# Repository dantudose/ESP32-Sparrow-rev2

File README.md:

# ESP32-Sparrow-rev2

The ESP32 Sparrow is a development board supporting the ESP32-WROVER module. It is fully Arduino-compatible and it comes with the following features:
* BME680 temperature, humidity, pressure and air quality sensor
* LTR308 ambient light sensor/luxmeter
* 128x32 SSD1306 OLED
* RGB LED
* I2S Microphone
* Micro-SD Card Holder
* 18650 LiPo battery holder with charging circuit
* Expansion headers
* USB charging/programming and data interface

<div id="cover">

</div>

Repository Contents
-------------------

* **/Hardware** - Eagle design files (.brd, .sch)
* **/Images** - Pinout and board images

Documentation
--------------
* **[Hookup Guide](https://ocw.cs.pub.ro/courses/iothings/laboratoare/2022/lab1)** - Basic hookup tutorial for ESP32 Sparrow

License Information
-------------------

This product is _**open source**_! 

Please review the LICENSE file for license information. 

Distributed as-is; no warranty is given.

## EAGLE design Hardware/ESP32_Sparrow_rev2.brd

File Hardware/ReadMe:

ESP32 Sparrow rev2 Eagle CAD files

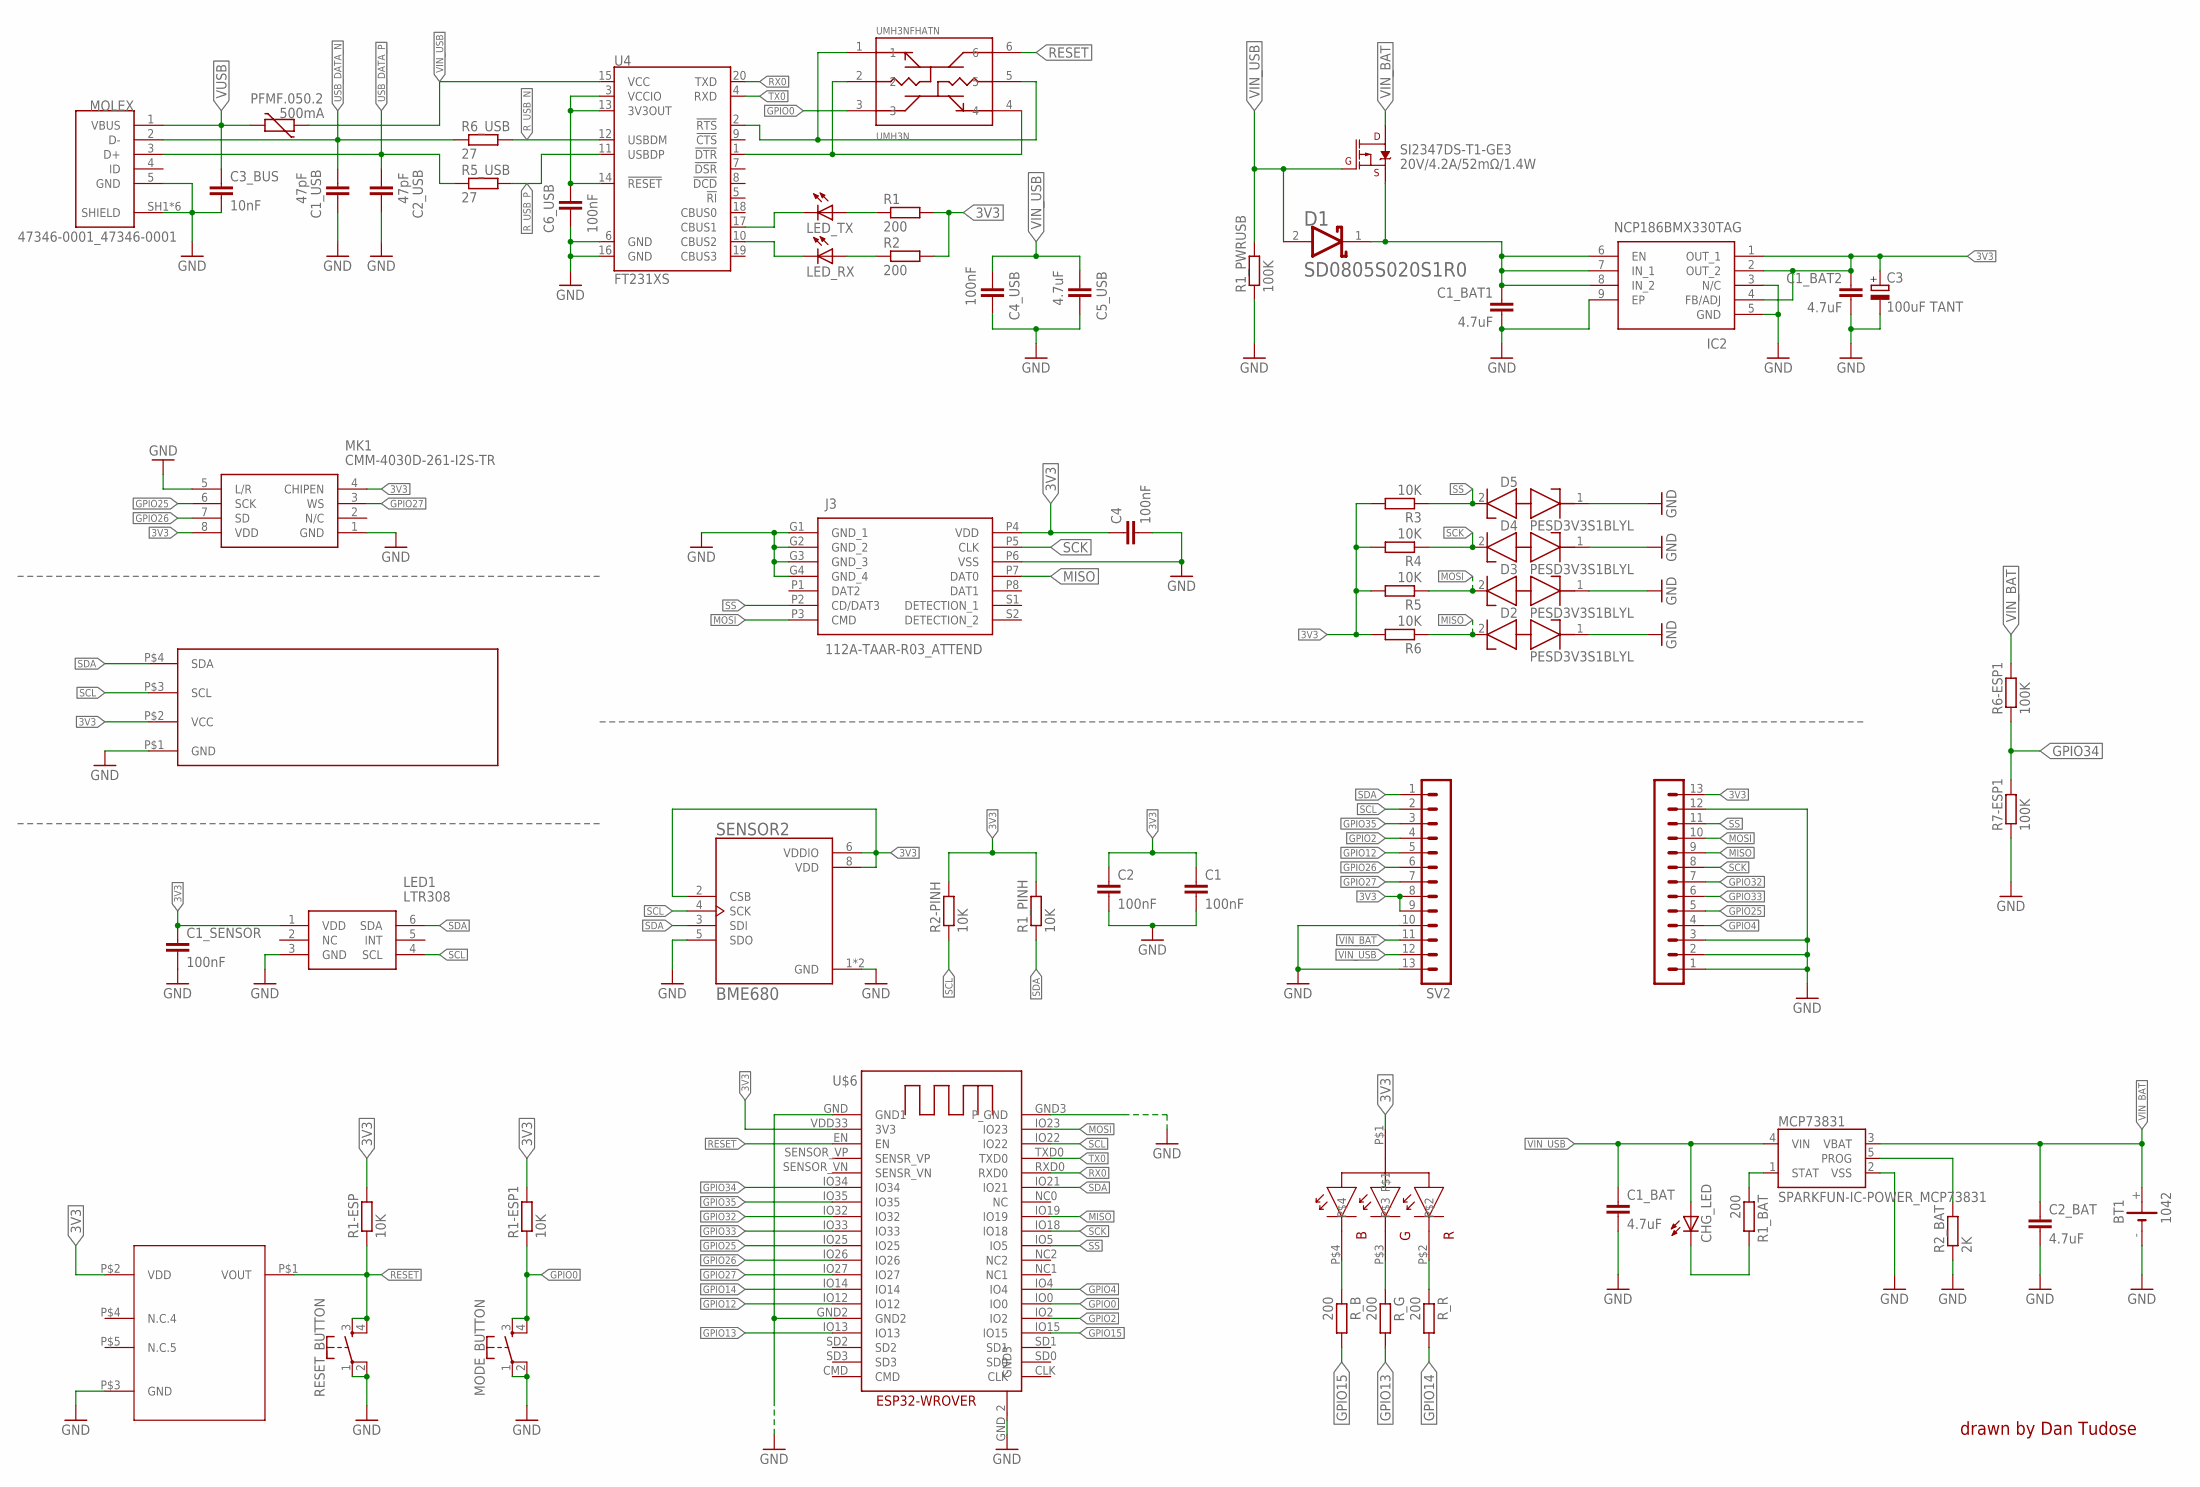
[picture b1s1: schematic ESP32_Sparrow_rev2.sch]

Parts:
BD48E27G-TR: BD48E27G-TR_BD48E27G-TR; BD48E27G-TR_SSOP5
BT1: 1042; BAT_1042
C1, C2, C4: 100nF; EAGLE-LTSPICE_C0402
C1_BAT, C1_BAT1, C1_BAT2, C2_BAT, C5_USB: 4.7uF; RCL_C0603
C1_SENSOR, C4_USB, C6_USB: 100nF; RCL_C0603
C1_USB, C2_USB: 47pF; RCL_C0603
C3: 100uF TANT; CT3528
C3_BUS: 10nF; RCL_C0603
CHG_LED: ADAFRUIT_LEDCHIP-LED0603; ADAFRUIT_CHIP-LED0603
D1: AVX---SD0805S020S1R0_AVX_SD0805S020S1R0AVX_SD0805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; AVX---SD0805S020S1R0_AVX_SD0805S020S1R0_0
D2, D3, D4, D5: PESD3V3S1BLYL; PESD5V0S1BL315
IC2: NCP186BMX330TAG; NCP186AMX330TAG
J3: 112A-TAAR-R03_ATTEND; 112ATAARR03ATTEND
LED1: LTR308; SAMACSYS_PARTS_LTR303ALS01
LED_RX: ADAFRUIT_LEDCHIP-LED0603; ADAFRUIT_CHIP-LED0603
LED_TX: ADAFRUIT_LEDCHIP-LED0603; ADAFRUIT_CHIP-LED0603
MCP73831: SPARKFUN-IC-POWER_MCP73831; SPARKFUN-IC-POWER_SOT23-5
MK1: CMM-4030D-261-I2S-TR; CMM4030D261I2STR
MODE_BUTTON: SPARKFUN-SWITCHES_MOMENTARY-SWITCH-SPST-2-SMD-4.6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; SPARKFUN-SWITCHES_TACTILE_SWITCH_SMD_4.6X2.8MM
MOLEX: 47346-0001_47346-0001; 47346-0001_MOLEX_47346-0001
PFMF.050.2: 500mA; VARISTOR_CT/CN1812
R1, R1_BAT, R2: 200; EAGLE-LTSPICE_R0402
R1-ESP, R1-ESP1, R1_PINH, R2-PINH, R3, R4, R5, R6: 10K; EAGLE-LTSPICE_R0402
R1_PWRUSB, R6-ESP1, R7-ESP1: 100K; EAGLE-LTSPICE_R0402
R2_BAT: 2K; EAGLE-LTSPICE_R0402
R5_USB, R6_USB: 27; EAGLE-LTSPICE_R0402
RESET_BUTTON: SPARKFUN-SWITCHES_MOMENTARY-SWITCH-SPST-2-SMD-4.6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; SPARKFUN-SWITCHES_TACTILE_SWITCH_SMD_4.6X2.8MM
R_B: 200; EAGLE-LTSPICE_R0402
R_G: 200; EAGLE-LTSPICE_R0402
R_R: 200; EAGLE-LTSPICE_R0402
SENSOR2: BME680; BME680_PSON80P300X300X100-8N
SI2347DS-T1-GE3: 20V/4.2A/52mΩ/1.4W; SPARKFUN-DISCRETESEMI_SOT23-3
SV1, SV2: MA13-1
U4: FT231XS; SPARKFUN-IC-COMMS_SSOP20_L
U$1: OLED; SIP
U$2: 150202M153130_150202M153130-RGB; 150202M153130_150202M153130
U$6: ESP32-WROVER_ESP32-WROVER
UMH3NFHATN: UMH3N; UMH3N_SOP65P210X100-6N

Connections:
3V3: BD48E27G-TR.P$2 (VDD), C1.1, C1_BAT2.1, C1_SENSOR.1, C2.1, C3.+, C4.1, IC2.1 (OUT_1), IC2.2 (OUT_2), IC2.4 (FB/ADJ), J3.P4 (VDD), LED1.1 (VDD), MK1.4 (CHIPEN), MK1.8 (VDD), R1.2, R1-ESP.2, R1-ESP1.2, R1_PINH.2, R2.2, R2-PINH.2, R3.2, R4.2, R5.2, R6.2, SENSOR2.2 (CSB), SENSOR2.6 (VDDIO), SENSOR2.8 (VDD), SV1.13, SV2.8, SV2.9, U$1.P$2 (VCC), U$2.P$1, U$6.VDD33 (3V3)
GND: BD48E27G-TR.P$3 (GND), BT1.-, C1.2, C1_BAT.2, C1_BAT1.2, C1_BAT2.2, C1_SENSOR.2, C1_USB.2, C2.2, C2_BAT.2, C2_USB.2, C3.-, C3_BUS.2, C4.2, C4_USB.2, C5_USB.2, C6_USB.2, D2.1 (K1), D3.1 (K1), D4.1 (K1), D5.1 (K1), IC2.3 (N/C), IC2.5 (GND), IC2.9 (EP), J3.G1 (GND_1), J3.G2 (GND_2), J3.G3 (GND_3), J3.G4 (GND_4), J3.P6 (VSS), LED1.3 (GND), MCP73831.2 (VSS), MK1.1 (GND), MK1.5 (L/R), MODE_BUTTON.1, MODE_BUTTON.2, MOLEX.5 (GND), MOLEX.SH1 (SHIELD), MOLEX.SH2 (SHIELD), MOLEX.SH3 (SHIELD), MOLEX.SH4 (SHIELD), MOLEX.SH5 (SHIELD), MOLEX.SH6 (SHIELD), R1_PWRUSB.1, R2_BAT.1, R7-ESP1.1, RESET_BUTTON.1, RESET_BUTTON.2, SENSOR2.1 (GND), SENSOR2.5 (SDO), SENSOR2.7 (GND), SV1.1, SV1.2, SV1.3, SV1.12, SV2.10, SV2.13, U4.6 (GND), U4.16 (GND), U$1.P$1 (GND), U$6.GND (GND1), U$6.GND2, U$6.GND3 (P_GND), U$6.GND_2 (GND3)
GPIO0: MODE_BUTTON.3, MODE_BUTTON.4, R1-ESP1.1, U$6.IO0, UMH3NFHATN.3
GPIO2: SV2.4, U$6.IO2
GPIO4: SV1.4, U$6.IO4
GPIO12: SV2.5, U$6.IO12
GPIO13: R_G.2, U$6.IO13
GPIO14: R_R.2, U$6.IO14
GPIO15: R_B.2, U$6.IO15
GPIO25: MK1.6 (SCK), SV1.5, U$6.IO25
GPIO26: MK1.7 (SD), SV2.6, U$6.IO26
GPIO27: MK1.3 (WS), SV2.7, U$6.IO27
GPIO32: SV1.7, U$6.IO32
GPIO33: SV1.6, U$6.IO33
GPIO34: R6-ESP1.1, R7-ESP1.2, U$6.IO34
GPIO35: SV2.3, U$6.IO35
MISO: D2.2 (K2), J3.P7 (DAT0), R6.1, SV1.9, U$6.IO19
MOSI: D3.2 (K2), J3.P3 (CMD), R5.1, SV1.10, U$6.IO23
unnamed: C1_BAT1.1, D1.1 (CATHODE), IC2.6 (EN), IC2.7 (IN_1), IC2.8 (IN_2), SI2347DS-T1-GE3.2 (S)
unnamed: MCP73831.1 (STAT), R1_BAT.1
unnamed: CHG_LED.C, R1_BAT.2
unnamed: MCP73831.5 (PROG), R2_BAT.2
unnamed: R_R.1, U$2.P$2
unnamed: R_G.1, U$2.P$3
unnamed: R_B.1, U$2.P$4
unnamed: C6_USB.1, U4.3 (VCCIO), U4.13 (3V3OUT), U4.14 (!RESET)
unnamed: LED_TX.A, R1.1
unnamed: LED_RX.A, R2.1
unnamed: U4.1 (!DTR), UMH3NFHATN.2, UMH3NFHATN.4
unnamed: LED_TX.C, U4.17 (CBUS1)
unnamed: LED_RX.C, U4.10 (CBUS2)
unnamed: U4.2 (!RTS), UMH3NFHATN.1, UMH3NFHATN.5
RESET: BD48E27G-TR.P$1 (VOUT), R1-ESP.1, RESET_BUTTON.3, RESET_BUTTON.4, U$6.EN, UMH3NFHATN.6
RX0: U4.20 (TXD), U$6.RXD0
R_USB_N: R6_USB.2, U4.12 (USBDM)
R_USB_P: R5_USB.2, U4.11 (USBDP)
SCK: D4.2 (K2), J3.P5 (CLK), R4.1, SV1.8, U$6.IO18
SCL: LED1.4 (SCL), R2-PINH.1, SENSOR2.4 (SCK), SV2.2, U$1.P$3 (SCL), U$6.IO22
SDA: LED1.6 (SDA), R1_PINH.1, SENSOR2.3 (SDI), SV2.1, U$1.P$4 (SDA), U$6.IO21
SS: D5.2 (K2), J3.P2 (CD/DAT3), R3.1, SV1.11, U$6.IO5
TX0: U4.4 (RXD), U$6.TXD0
USB_DATA_N: C1_USB.1, MOLEX.2 (D-), R6_USB.1
USB_DATA_P: C2_USB.1, MOLEX.3 (D+), R5_USB.1
VIN_BAT: BT1.+, C2_BAT.1, MCP73831.3 (VBAT), R6-ESP1.2, SI2347DS-T1-GE3.3 (D), SV2.11
VIN_USB: C1_BAT.1, C4_USB.1, C5_USB.1, CHG_LED.A, D1.2 (ANODE), MCP73831.4 (VIN), PFMF.050.2.1, R1_PWRUSB.2, SI2347DS-T1-GE3.1 (G), SV2.12, U4.15 (VCC)
VUSB: C3_BUS.1, MOLEX.1 (VBUS), PFMF.050.2.2

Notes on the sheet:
drawn by Dan Tudose

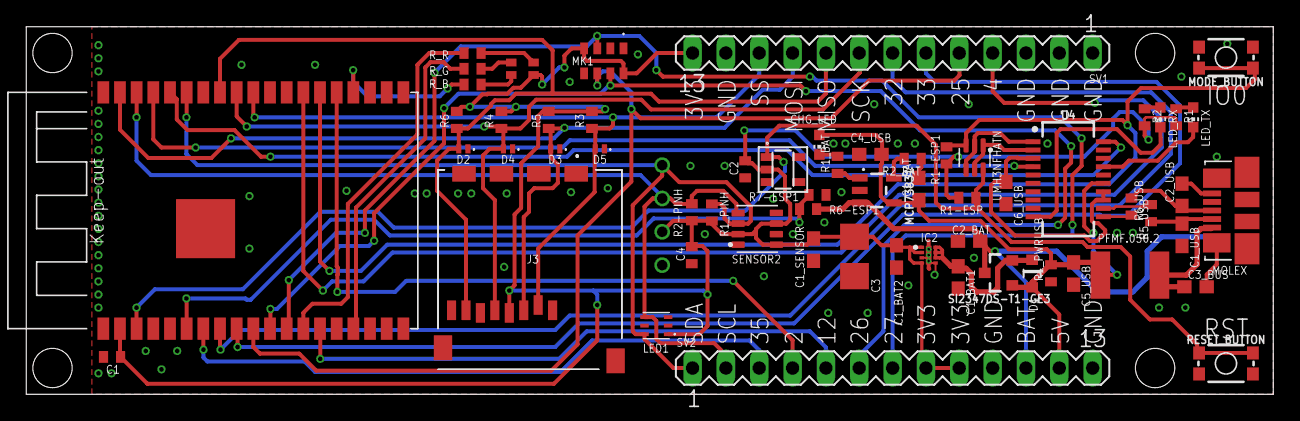
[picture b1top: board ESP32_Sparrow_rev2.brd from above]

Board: 2 copper layers, 95.0 x 28.0 mm, 63 parts (1 on the bottom side), 46 nets.
